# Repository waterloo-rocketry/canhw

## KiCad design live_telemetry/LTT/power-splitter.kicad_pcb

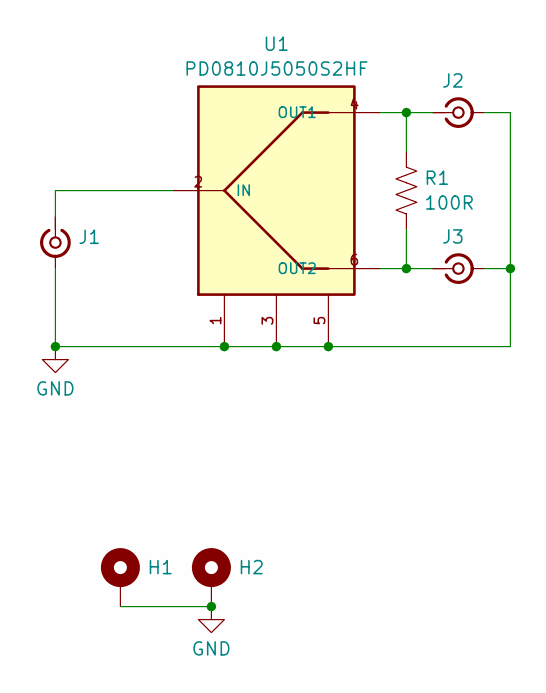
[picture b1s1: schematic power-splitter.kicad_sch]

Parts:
H1, H2: MountingHole_Pad; MountingHole_3.2mm_M3_Pad_Via
J1, J2, J3: Conn_Coaxial_Small; TAOGLAS_EMPCB.SMAFSTJ.B.HT
R1: 100R; R_0603_1608Metric_Pad0.98x0.95mm_HandSolder
U1: PD0810J5050S2HF; DigiKey_Part_Number 1173-1093-1-ND

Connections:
GND: H1.1, H2.1, J1.2 (Ext), J2.2 (Ext), J3.2 (Ext), U1.1, U1.3, U1.5
unnamed: J1.1 (In), U1.2 (IN)
unnamed: J2.1 (In), R1.1, U1.4 (OUT1)
unnamed: J3.1 (In), R1.2, U1.6 (OUT2)

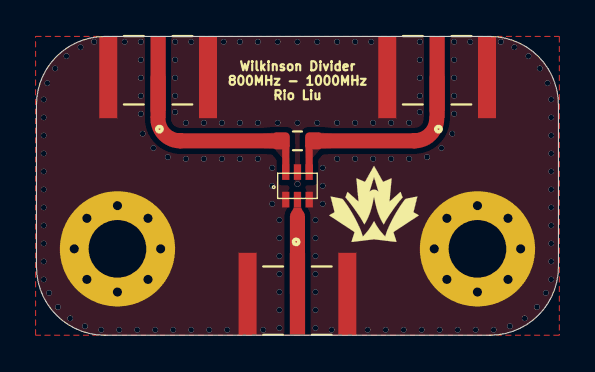
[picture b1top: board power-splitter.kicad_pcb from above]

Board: 2 copper layers, 29.0 x 16.6 mm, 7 parts (0 on the bottom side), 4 nets.

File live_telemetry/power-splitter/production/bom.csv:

Designator,Footprint,Quantity,Value,LCSC Part #
"J1, J2, J3",TAOGLAS_EMPCB.SMAFSTJ.B.HT,3,Conn_Coaxial_Small,
R1,0603,1,100R,
U1,PD0810J5050S2HF,1,PD0810J5050S2HF,

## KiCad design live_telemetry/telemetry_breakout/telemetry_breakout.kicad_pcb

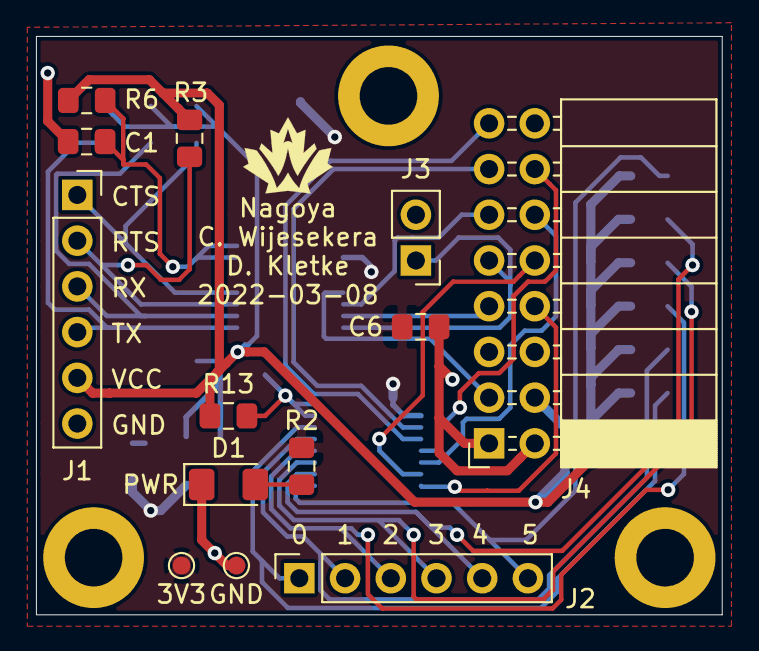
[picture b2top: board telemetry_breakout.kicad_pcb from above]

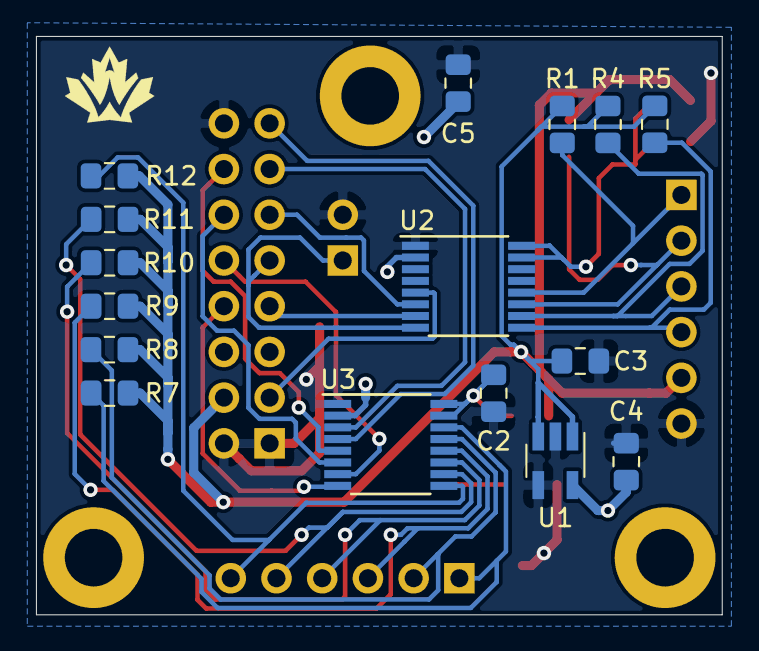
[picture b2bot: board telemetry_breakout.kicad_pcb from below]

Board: 2 copper layers, 38.1 x 32.1 mm, 29 parts (16 on the bottom side), 26 nets.

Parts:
C1, C2, C5, C6: 0.1u; C_0805_2012Metric_Pad1.15x1.40mm_HandSolder
C3, C4: 1u; C_0805_2012Metric_Pad1.15x1.40mm_HandSolder
D1: LED_White; LED_1206_3216Metric_Pad1.42x1.75mm_HandSolder
J1: Conn_01x06_Male; PinSocket_1x06_P2.54mm_Vertical
J2: 0.1in_Header_Pins_01x06; PinSocket_1x06_P2.54mm_Vertical
J3: Bootload Short; PinHeader_1x02_P2.54mm_Vertical
J4: RFD900x RADIO MODEM CONN; PinSocket_2x08_P2.54mm_Horizontal
R1, R3, R4, R5, R7, R8, R9, R10, R11, R12: 2k; R_0805_2012Metric_Pad1.15x1.40mm_HandSolder
R2: 50; R_0805_2012Metric_Pad1.15x1.40mm_HandSolder
R6, R13: 200k; R_0805_2012Metric_Pad1.15x1.40mm_HandSolder
TP1: Test_3V3; TestPoint_Pad_D1.0mm
TP2: Test_GND; TestPoint_Pad_D1.0mm
U1: 497-18013-1-ND; SOT-23-5_HandSoldering
U2, U3: NVT2006PW; TSSOP-16_4.4x5mm_P0.65mm

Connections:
+3V3: C4.1, C5.2, C6.2, R2.1, TP1.1, U1.5, U2.2, U3.2
+5V: C3.2, J1.5, J4.4, R1.1, R3.1, R4.1, R5.1, R6.1, R7.1, R8.1, R9.1, R10.1, R11.1, R12.1, R13.1, U1.1, U1.3
/EN1: C1.2, R6.2, U2.15, U2.16
/EN2: C2.2, R13.2, U3.15, U3.16
/GPIO0: J4.13, U3.3
/GPIO0_H: J2.1, R7.2, U3.14
/GPIO1: J4.15, U3.4
/GPIO1_H: J2.2, R8.2, U3.13
/GPIO2: J4.14, U3.5
/GPIO2_H: J2.3, R9.2, U3.12
/GPIO3: J4.12, U3.6
/GPIO3_H: J2.4, R10.2, U3.11
/GPIO4: J4.10, U3.7
/GPIO4_H: J2.5, R11.2, U3.10
/GPIO5: J4.8, U3.8
/GPIO5_H: J2.6, R12.2, U3.9
/RX: J4.7, U2.7
/RX_H: J1.3, R4.2, U2.10
/TX: J3.1, J4.9, U2.8
/TX_H: J1.4, R5.2, U2.9
/~CTS: J4.3, U2.5
/~CTS_H: J1.1, R1.2, U2.12
/~RTS: J4.11, U2.6
/~RTS_H: J1.2, R3.2, U2.11
GND: C1.1, C2.1, C3.1, C4.2, C5.1, C6.1, D1.1, J1.6, J3.2, J4.1, J4.2, J4.16, TP2.1, U1.2, U1.4, U2.1, U3.1
unnamed: D1.2, R2.2

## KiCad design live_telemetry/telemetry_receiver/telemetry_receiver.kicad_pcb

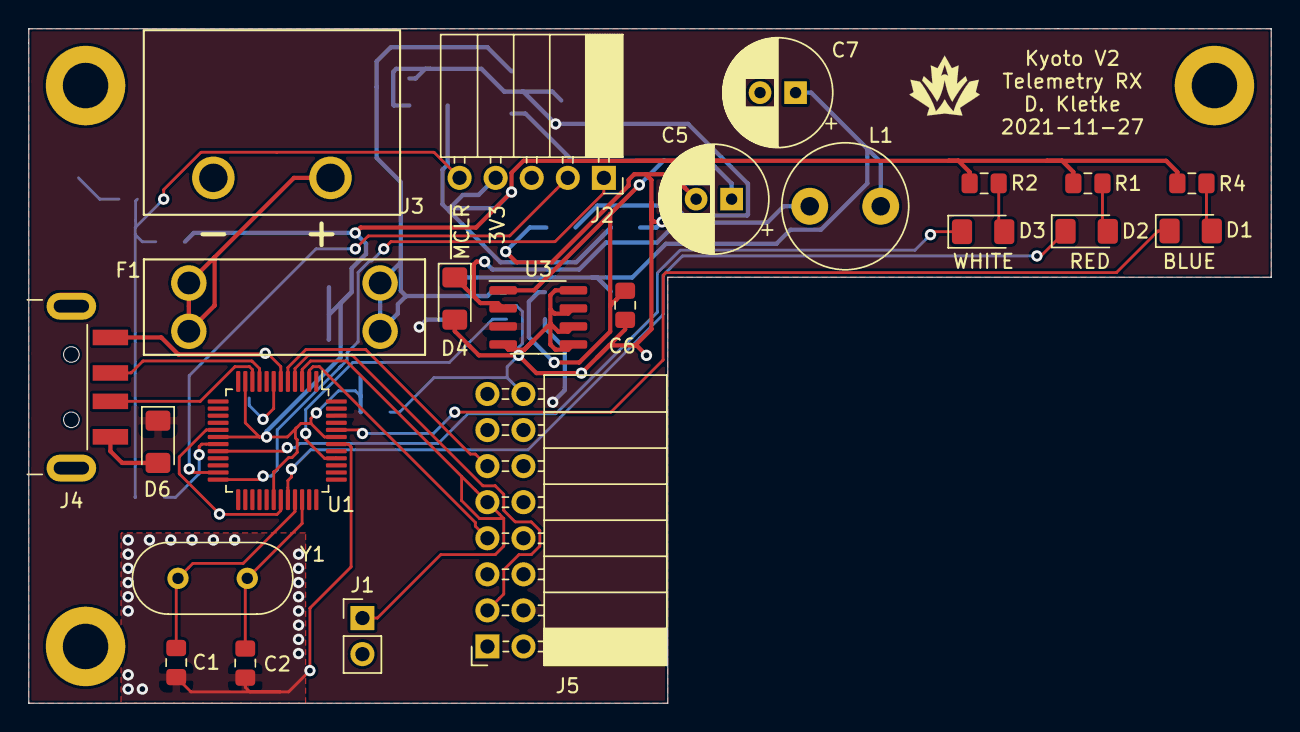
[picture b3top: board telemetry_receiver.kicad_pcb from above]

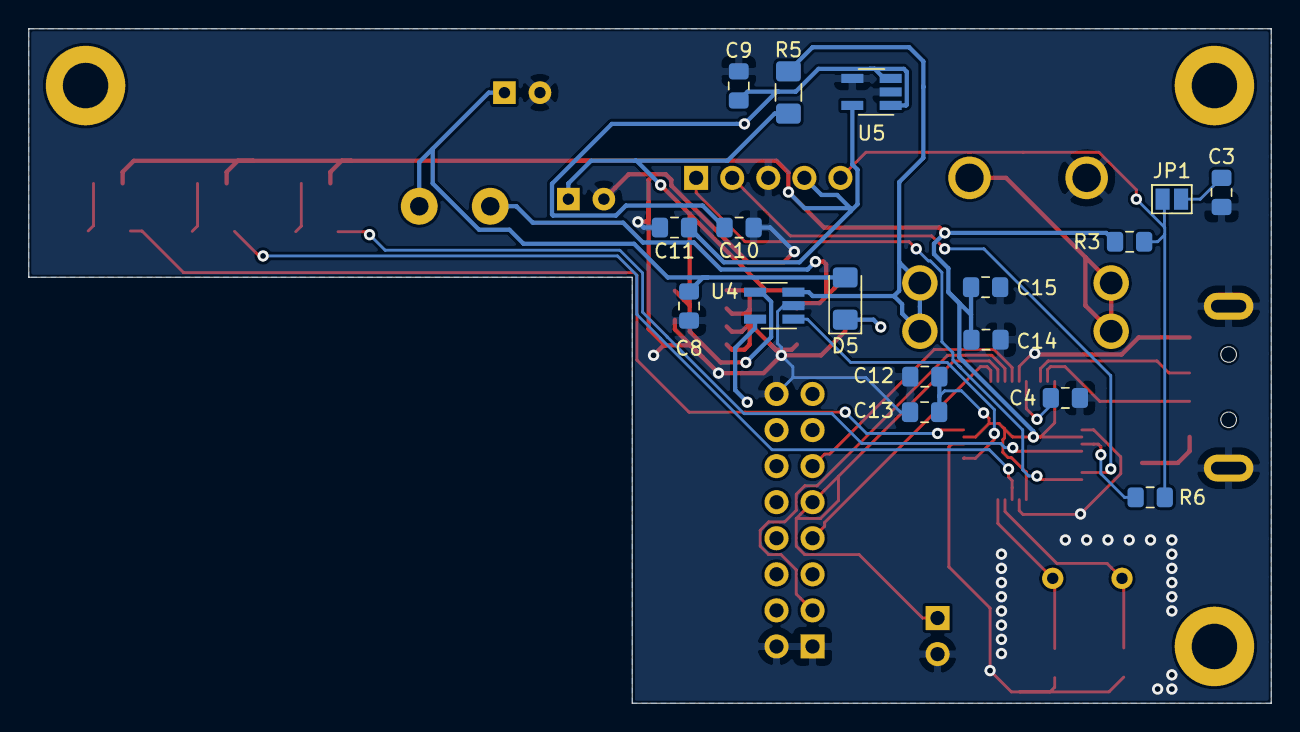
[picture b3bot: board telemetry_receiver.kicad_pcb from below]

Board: 2 copper layers, 87.5 x 47.5 mm, 40 parts (17 on the bottom side), 30 nets.

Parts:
C1, C2: 27pF; C_0805_2012Metric_Pad1.15x1.40mm_HandSolder
C3, C6, C8, C9, C12, C13, C14, C15: 0.1uF; C_0805_2012Metric_Pad1.15x1.40mm_HandSolder
C4: 10uF; C_0805_2012Metric_Pad1.15x1.40mm_HandSolder
C5, C7: 100uF; CP_Radial_D7.5mm_P2.50mm
C10, C11: 1uF; C_0805_2012Metric_Pad1.15x1.40mm_HandSolder
D1, D2, D3: LED; LED_1206_3216Metric_Pad1.42x1.75mm_HandSolder
D4, D5, D6: SD1206S040S2R0; D_1206_3216Metric_Pad1.42x1.75mm_HandSolder
F1: F4989-ND, 36-3557-2-ND; Fuseholder_36-3557-15-ND
J1: Bootload Short; PinHeader_1x02_P2.54mm_Vertical
J2: Programming Header; PinSocket_1x05_P2.54mm_Horizontal
J3: Battery In; BarrierBlock_ED2945-ND
J4: USB_A; USB_A_CNCTech_1001-011-01101_Horizontal
J5: RFD900x RADIO MODEM CONN; PinSocket_2x08_P2.54mm_Horizontal
JP1: Jumper_2_Open; SolderJumper-2_P1.3mm_Open_Pad1.0x1.5mm
L1: 47uH; L_Radial_D8.7mm_P5.00mm_Fastron_07HCP
R1, R2, R4: 130; R_0805_2012Metric_Pad1.15x1.40mm_HandSolder
R3: 10k; R_0805_2012Metric_Pad1.15x1.40mm_HandSolder
R5: R_sense; R_1206_3216Metric_Pad1.42x1.75mm_HandSolder
R6: 100R; R_0805_2012Metric_Pad1.15x1.40mm_HandSolder
U1: PIC24FJ64GU205; TQFP-48_7x7mm_P0.5mm
U3: AP1509; SOIC-8_3.9x4.9mm_P1.27mm
U4: INA180; SOT-23-5_HandSoldering
U5: TLV70233QDBVRQ1; SOT-23-5_HandSoldering
Y1: Crystal; Crystal_HC49-U_Vertical

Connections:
+3V3: C11.1, C12.1, C13.1, C14.1, C15.1, J2.4, R1.1, R2.1, R3.1, R4.1, U1.11, U1.18, U1.30, U1.43, U5.5
+5V: C9.2, C10.1, D5.1, D6.1, J5.4, U1.46, U3.3, U4.5, U5.1, U5.3
+12V: C5.1, C6.1, R5.1, U3.1, U4.4
/ICSPCLK: J2.1, U1.24
/ICSPDAT: J2.2, U1.23
/OSC1: C1.1, U1.33, Y1.1
/OSC2: C2.2, U1.34, Y1.2
/USB_D+: J4.3, U1.9
/USB_D-: J4.2, U1.10
/power/CURR_BATT: U1.40, U4.1
/radio.sch/RX: J5.7, U1.2
/radio.sch/TX: J1.1, J5.9, U1.3
/radio.sch/~CTS: J5.3, U1.4
/radio.sch/~RTS: J5.11, U1.5
/~MCLR: J2.5, JP1.2, R3.2, R6.1
GND: C1.2, C2.1, C3.2, C4.2, C5.2, C6.2, C7.2, C8.2, C9.1, C10.2, C11.2, C12.2, C13.2, C14.2, C15.2, D4.2, J1.2, J2.3, J3.1, J4.4, J4.5, J5.1, J5.2, J5.16, U1.6, U1.17, U1.31, U1.42, U3.4, U3.5, U3.6, U3.7, U3.8, U4.2, U5.2, U5.4
unnamed: C3.1, JP1.1
unnamed: C4.1, U1.7
unnamed: C7.1, C8.1, D5.2, L1.2
unnamed: D1.1, U1.44
unnamed: D1.2, R4.2
unnamed: D2.1, U1.32
unnamed: D2.2, R1.2
unnamed: D3.1, U1.20
unnamed: D3.2, R2.2
unnamed: D4.1, L1.1, U3.2
unnamed: D6.2, J4.1
unnamed: F1.1, R5.2, U4.3
unnamed: F1.2, J3.2
unnamed: R6.2, U1.19

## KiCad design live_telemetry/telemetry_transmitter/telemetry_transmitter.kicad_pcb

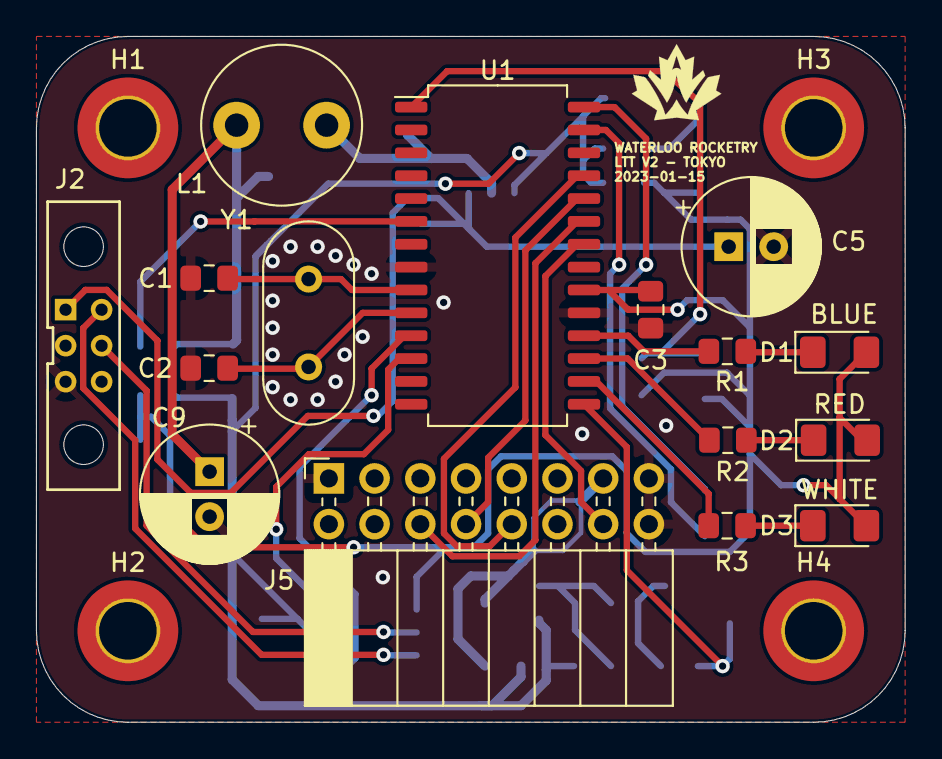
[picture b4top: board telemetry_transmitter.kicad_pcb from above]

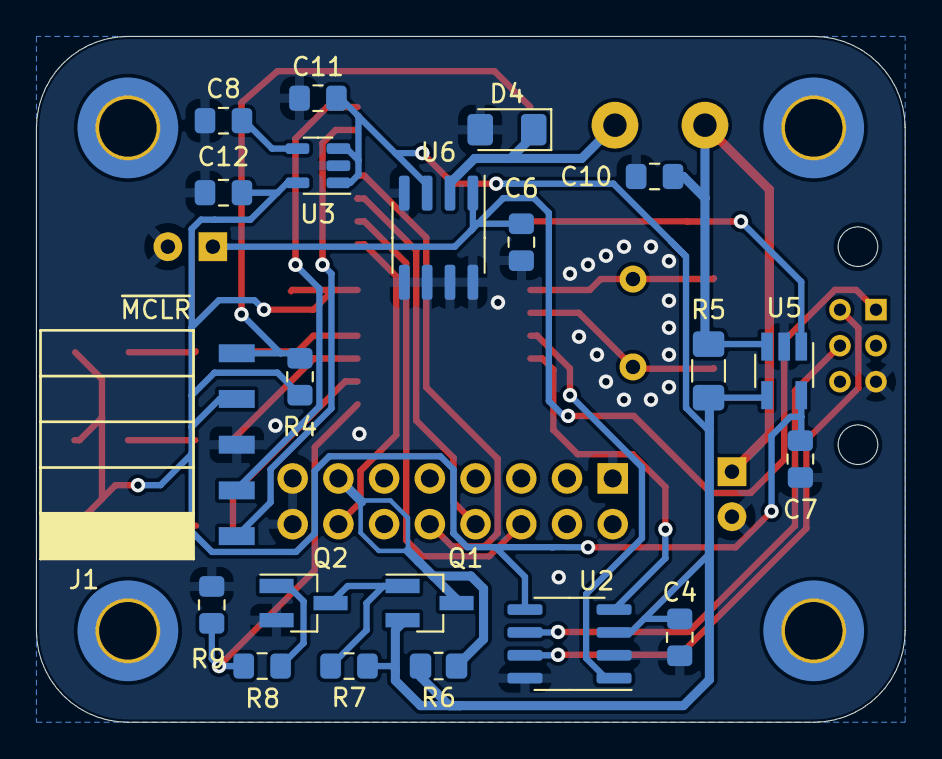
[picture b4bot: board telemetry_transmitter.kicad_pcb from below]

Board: 2 copper layers, 48.3 x 38.1 mm, 41 parts (21 on the bottom side), 31 nets.

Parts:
C1, C2: 27pF; C_0805_2012Metric_Pad1.15x1.40mm_HandSolder
C3, C6, C7, C10: 0.1u; C_0805_2012Metric_Pad1.15x1.40mm_HandSolder
C4: 10u; C_0805_2012Metric_Pad1.15x1.40mm_HandSolder
C5, C9: 100u; CP_Radial_D7.5mm_P2.50mm
C8: 10nF; C_0805_2012Metric_Pad1.15x1.40mm_HandSolder
C11: 10uF; C_0805_2012Metric_Pad1.15x1.40mm_HandSolder
C12: 2.2uF; C_0805_2012Metric_Pad1.15x1.40mm_HandSolder
D1, D2, D3: LED; LED_1206_3216Metric_Pad1.42x1.75mm_HandSolder
D4: SD1206S040S2R0; D_1206_3216Metric_Pad1.42x1.75mm_HandSolder
H1, H2, H3, H4: MountingHole; MountingHole_3.2mm_M3_DIN965_Pad_TopBottom
J1: Programming Header; PinHeader_5x2.54_SMD_90deg_952-3198-1-ND
J2: BUS_CONN; connector_Harwin_M80-5000642
J5: RFD900x; PinSocket_2x08_P2.54mm_Horizontal
L1: 47u; L_Radial_D8.7mm_P5.00mm_Fastron_07HCP
Q1: PJA3405; SOT-23_Handsoldering
Q2: TSM2306CX; SOT-23_Handsoldering
R1, R2, R3, R8: 130; R_0805_2012Metric_Pad1.15x1.40mm_HandSolder
R4, R7, R9: 10K; R_0805_2012Metric_Pad1.15x1.40mm_HandSolder
R5: 0.02R; R_1206_3216Metric_Pad1.42x1.75mm_HandSolder
R6: DNI; R_0805_2012Metric_Pad1.20x1.40mm_HandSolder
U1: PIC18F26K83; SOIC-28W_7.5x18.7mm_P1.27mm
U2: MCP2562; SOIC-8_3.9x4.9mm_P1.27mm
U3: SPX3819M5-L-3-3/TR; SOT-23-5
U5: INA180; SOT-23-5_HandSoldering
U6: AP1509-50SG-13; SOIC-8_3.9x4.9mm_P1.27mm
Y1: Crystal; Crystal_HC49-U_Vertical

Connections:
+3V3: C3.1, C7.2, C12.2, D1.2 (A), D2.2 (A), D3.2 (A), J1.4, R4.1, U1.20 (VDD), U2.5 (VIO), U3.5 (OUT), U5.5 (VS)
+5V: C4.1, C11.2, Q1.2 (S), R5.1, R6.2, R7.1, U2.3 (VDD), U3.1 (IN), U3.3 (EN), U5.4 (IN-), U6.3 (FB)
+12V: C5.1, C6.2, J2.1, U6.1 (Vin)
/CAN_H: J2.4, U2.7 (CANH)
/CAN_L: J2.5, U2.6 (CANL)
/CAN_RX: U1.12 (RC1), U2.4 (RXD)
/CAN_TX: U1.11 (RC0), U2.1 (TXD)
/CTS: J5.14, U1.22 (RB1)
/ICSPCLK: J1.1, U1.27 (RB6/ICSPCLK)
/ICSPDAT: J1.2, U1.28 (RB7/ICSPDAT)
/LED1: R1.2, U1.18 (RC7)
/LED2: R2.2, U1.17 (RC6)
/LED3: R3.2, U1.16 (RC5)
/OSC1: C1.1, U1.9 (RA7/OSC1), Y1.1
/OSC2: C2.1, U1.10 (RA6/OSC2), Y1.2
/RADIO_OFF: R8.2, R9.1, U1.15 (RC4)
/RTS: J5.6, U1.23 (RB2)
/RX: J5.10, U1.25 (RB4)
/TX: J5.8, U1.24 (RB3)
/power/CURR_LTT: U1.6 (RA4), U5.1 (VO)
/~MCLR: J1.5, R4.2, U1.1 (~MCLR)
GND: C1.2, C2.2, C3.2, C4.2, C5.2, C6.1, C7.1, C8.1, C9.2, C10.1, C11.1, C12.1, D4.2 (A), J1.3, J2.3, J5.1, J5.15, J5.16, Q2.2 (S), R9.2, U1.8 (VSS), U1.19 (VSS), U2.2 (VSS), U2.8 (STBY), U3.2 (GND), U5.2 (GND), U6.4 (SD), U6.5 (GND), U6.6 (GND), U6.7 (GND), U6.8 (GND)
unnamed: C8.2, U3.4 (BP)
unnamed: C9.1, C10.2, L1.2, R5.2, U5.3 (IN+)
unnamed: D1.1 (K), R1.1
unnamed: D2.1 (K), R2.1
unnamed: D3.1 (K), R3.1
unnamed: D4.1 (K), L1.1, U6.2 (Output)
unnamed: J5.13, Q1.3 (D), R6.1
unnamed: Q1.1 (G), Q2.3 (D), R7.2
unnamed: Q2.1 (G), R8.1

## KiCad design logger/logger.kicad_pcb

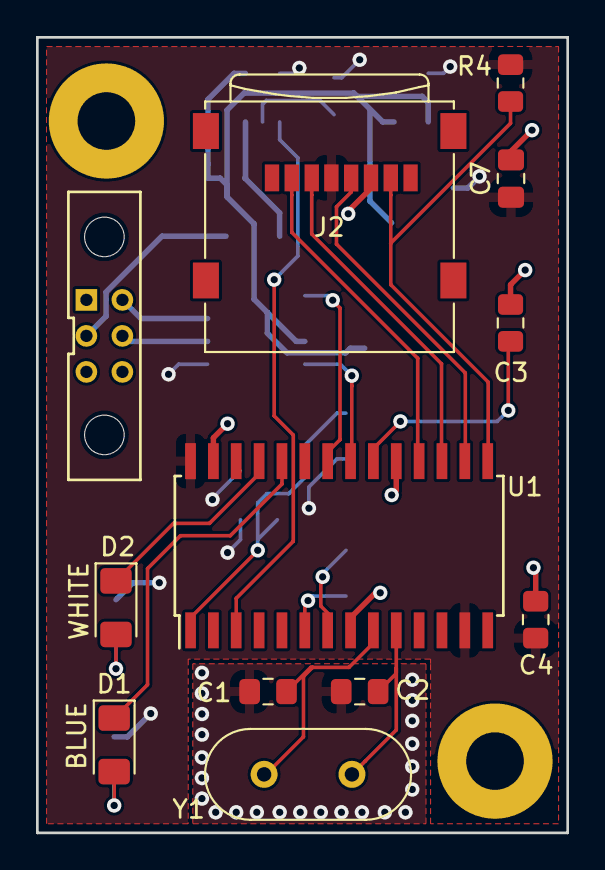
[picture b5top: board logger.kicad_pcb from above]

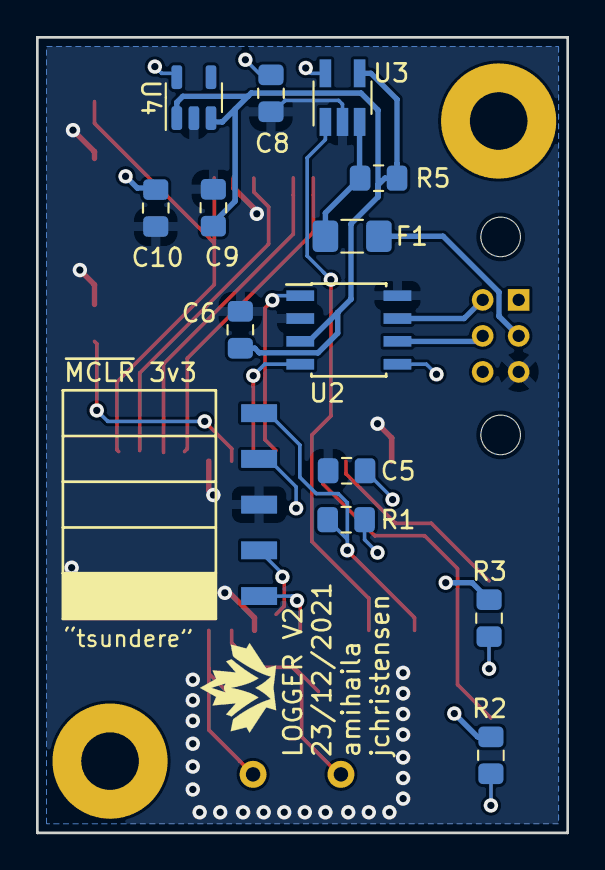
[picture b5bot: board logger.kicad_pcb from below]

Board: 2 copper layers, 29.5 x 44.2 mm, 26 parts (14 on the bottom side), 24 nets.

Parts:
C1, C2: 27pF; C_0805_2012Metric_Pad1.15x1.40mm_HandSolder
C3, C6: 10uF; C_0805_2012Metric_Pad1.15x1.40mm_HandSolder
C4, C5, C8: 0.1uF; C_0805_2012Metric_Pad1.15x1.40mm_HandSolder
C7: 4.7uF; C_0805_2012Metric_Pad1.18x1.45mm_HandSolder
C9, C10: 4.7uF; C_0805_2012Metric_Pad1.15x1.40mm_HandSolder
D1: DEBUG1; LED_1206_3216Metric_Pad1.42x1.75mm_HandSolder
D2: DEBUG2; LED_1206_3216Metric_Pad1.42x1.75mm_HandSolder
F1: Polyfuse 350mA; Fuse_1206_3216Metric_Pad1.42x1.75mm_HandSolder
J1: Programming; PinHeader_5x2.54_SMD_90deg_952-3198-1-ND
J2: Micro_SD_Card; microSD_Molex_WM6698CT-ND
J3: CAN CONN; connector_Harwin_M80-5000642
R1: 10K; R_0805_2012Metric_Pad1.15x1.40mm_HandSolder
R2, R3: 160R; R_0805_2012Metric_Pad1.15x1.40mm_HandSolder
R4: 10k; R_0805_2012Metric_Pad1.15x1.40mm_HandSolder
R5: 62mR; R_0805_2012Metric_Pad1.15x1.40mm_HandSolder
U1: DSPIC33EP512GP502; SOIC-28W_7.5x17.9mm_P1.27mm
U2: MCP2562; SOIC-8_3.9x4.9mm_P1.27mm
U3: INA180; SOT-23-5_HandSoldering
U4: SPX3819M5-L-3-3; SOT-23-5
Y1: Crystal; Crystal_HC49-4H_Vertical

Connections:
+3V3: C4.1, C5.2, C7.1, C8.2, C10.2, J1.4, J2.4 (VDD), R1.1, R2.1, R3.1, R4.1, U1.13 (VDD), U1.28 (AVDD), U2.5 (VIO), U3.5 (VS), U4.5 (OUT)
+5V: C6.1, C9.2, R5.1, U2.3 (VDD), U3.4 (IN-), U4.1 (IN), U4.3 (EN)
/CANRX: U1.21 (TDO/RP42/RB10), U2.4 (RXD)
/CANTX: U1.22 (TDI/RP43/RB11), U2.1 (TXD)
/ICSPCLK: J1.1, U1.6 (PGEC1/AN4/C1IN1+/RPI34/RB2)
/ICSPDAT: J1.2, U1.7 (PGED1/AN5/C1IN1-/RP35/RB3)
/OSC1: C1.1, U1.9 (OSC1/CLKI/RA2), Y1.1
/OSC2: C2.1, U1.10 (OSC2/CLKO/RA3), Y1.2
/SD1_CS: J2.2 (DAT3/CD), U1.18 (TMS/ASDA1/SDI1/RP41/RB9)
/SD1_MISO: J2.7 (DAT0), R4.2, U1.15 (PGEC2/ASCL2/RP38/RB6)
/SD1_MOSI: J2.3 (CMD), U1.17 (TCK/CVREF1O/ASCL1/SDO1/RP40/T4CK/RB8)
/SD1_SCLK: J2.5 (CLK), U1.16 (SCK1/RP39/INT0/RB7)
/~MCLR: J1.5, R1.2, U1.1 (~MCLR)
CANH: J3.4, U2.7 (CANH)
CANL: J3.5, U2.6 (CANL)
CURR_AMP: U1.3 (AN1/C2IN1+/RA1), U3.1 (VO)
GND: C1.2, C2.2, C3.2, C4.2, C5.1, C6.2, C7.2, C8.1, C9.1, C10.1, J1.3, J2.6 (VSS), J3.3, U1.8 (VSS), U1.19 (VSS), U1.27 (AVSS), U2.2 (VSS), U2.8 (STBY), U3.2 (GND), U4.2 (GND)
unnamed: C3.1, U1.20 (VCAP)
unnamed: D1.1 (K), U1.24 (RPI45/CTPLS/RB13)
unnamed: D1.2 (A), R2.2
unnamed: D2.1 (K), U1.25 (RPI46/T3CK/RB14)
unnamed: D2.2 (A), R3.2
unnamed: F1.1, R5.2, U3.3 (IN+)
unnamed: F1.2, J3.2

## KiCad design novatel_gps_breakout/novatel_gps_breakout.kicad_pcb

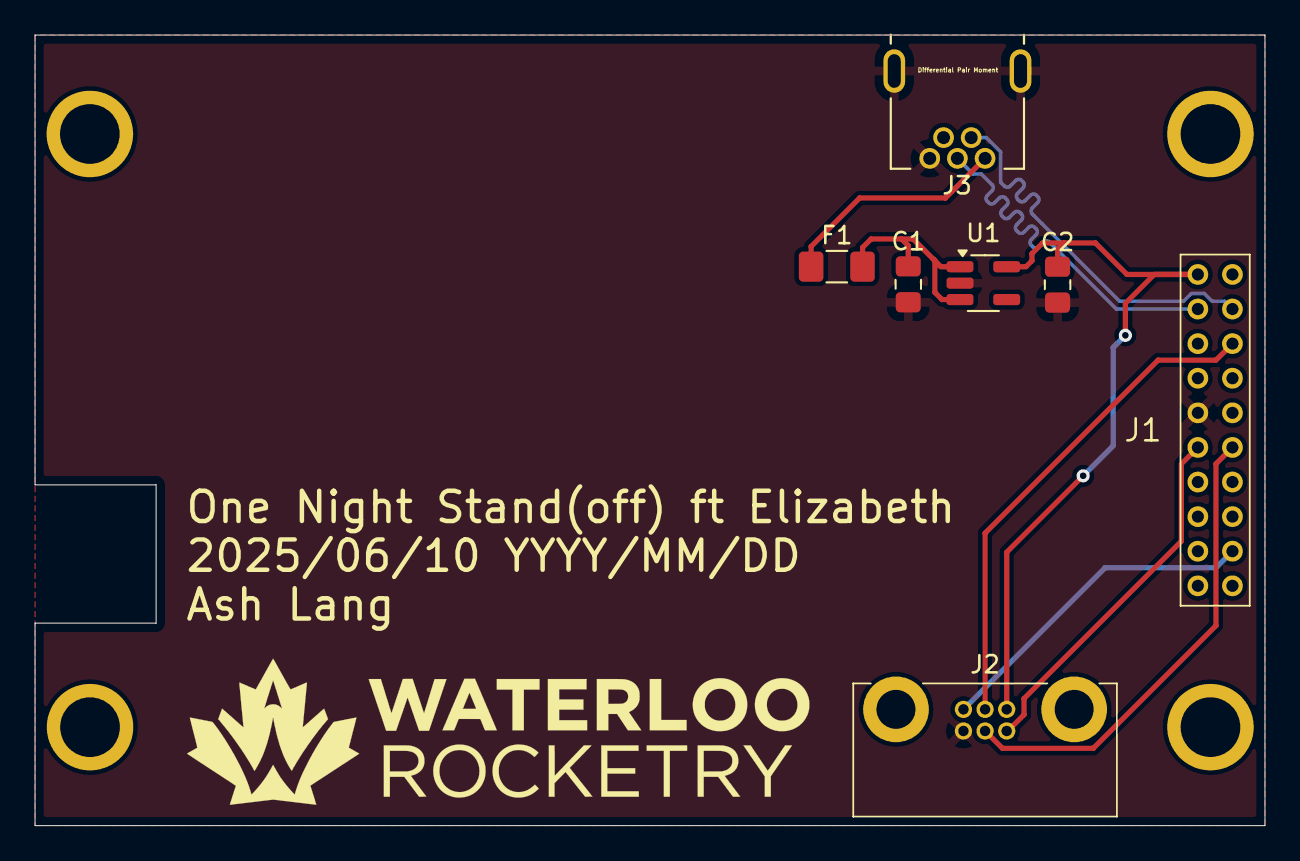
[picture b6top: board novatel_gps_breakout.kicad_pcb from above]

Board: 2 copper layers, 71.1 x 45.7 mm, 11 parts (0 on the bottom side), 10 nets.

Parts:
C1, C2: 10u; C_0805_2012Metric_Pad1.18x1.45mm_HandSolder
F1: 350m; Fuse_1206_3216Metric_Pad1.42x1.75mm_HandSolder
H1, H2, H3, H4: MountingHole; 4-40
J1: PTF-110-01-L-D; PTF11001LD
J2: Harwin Gecko; connector_Harwin_G125–MG10605M4P
J3: GMSB0522132EU; AMPHENOL_GMSB0522132EU
U1: TLV75533PDBV; SOT-23-5_HandSoldering

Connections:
+3V3: C2.1, J1.2, J2.1, U1.5 (OUT)
/GPS_PV: J1.17, J2.3
/UART_RX: J1.12, J2.4
/UART_TX: J1.11, J2.5
/USB_D+: J1.4, J3.3 (D+)
/USB_D-: J1.3, J3.2 (D-)
/~GPS_RESET: J1.5, J2.2
GND: C1.2, C2.2, J1.10, J2.6, J3.5 (GND), J3.6 (Shield), U1.2 (GND)
unnamed: F1.1, J3.1 (VBUS)
unnamed: C1.1, F1.2, U1.1 (IN), U1.3 (EN)

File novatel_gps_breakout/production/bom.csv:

Designator,Footprint,Quantity,Value,LCSC Part #
"C1, C2",0805,2,10u,
F1,1206,1,350m,
J1,PTF11001LD,1,PTF-110-01-L-D,
J2,connector_Harwin_G125–MG10605M4P,1,Altimeter Connector,
J3,AMPHENOL_GMSB0522132EU,1,GMSB0522132EU,
U1,SOT-23-5_HandSoldering,1,TLV75533PDBV,
